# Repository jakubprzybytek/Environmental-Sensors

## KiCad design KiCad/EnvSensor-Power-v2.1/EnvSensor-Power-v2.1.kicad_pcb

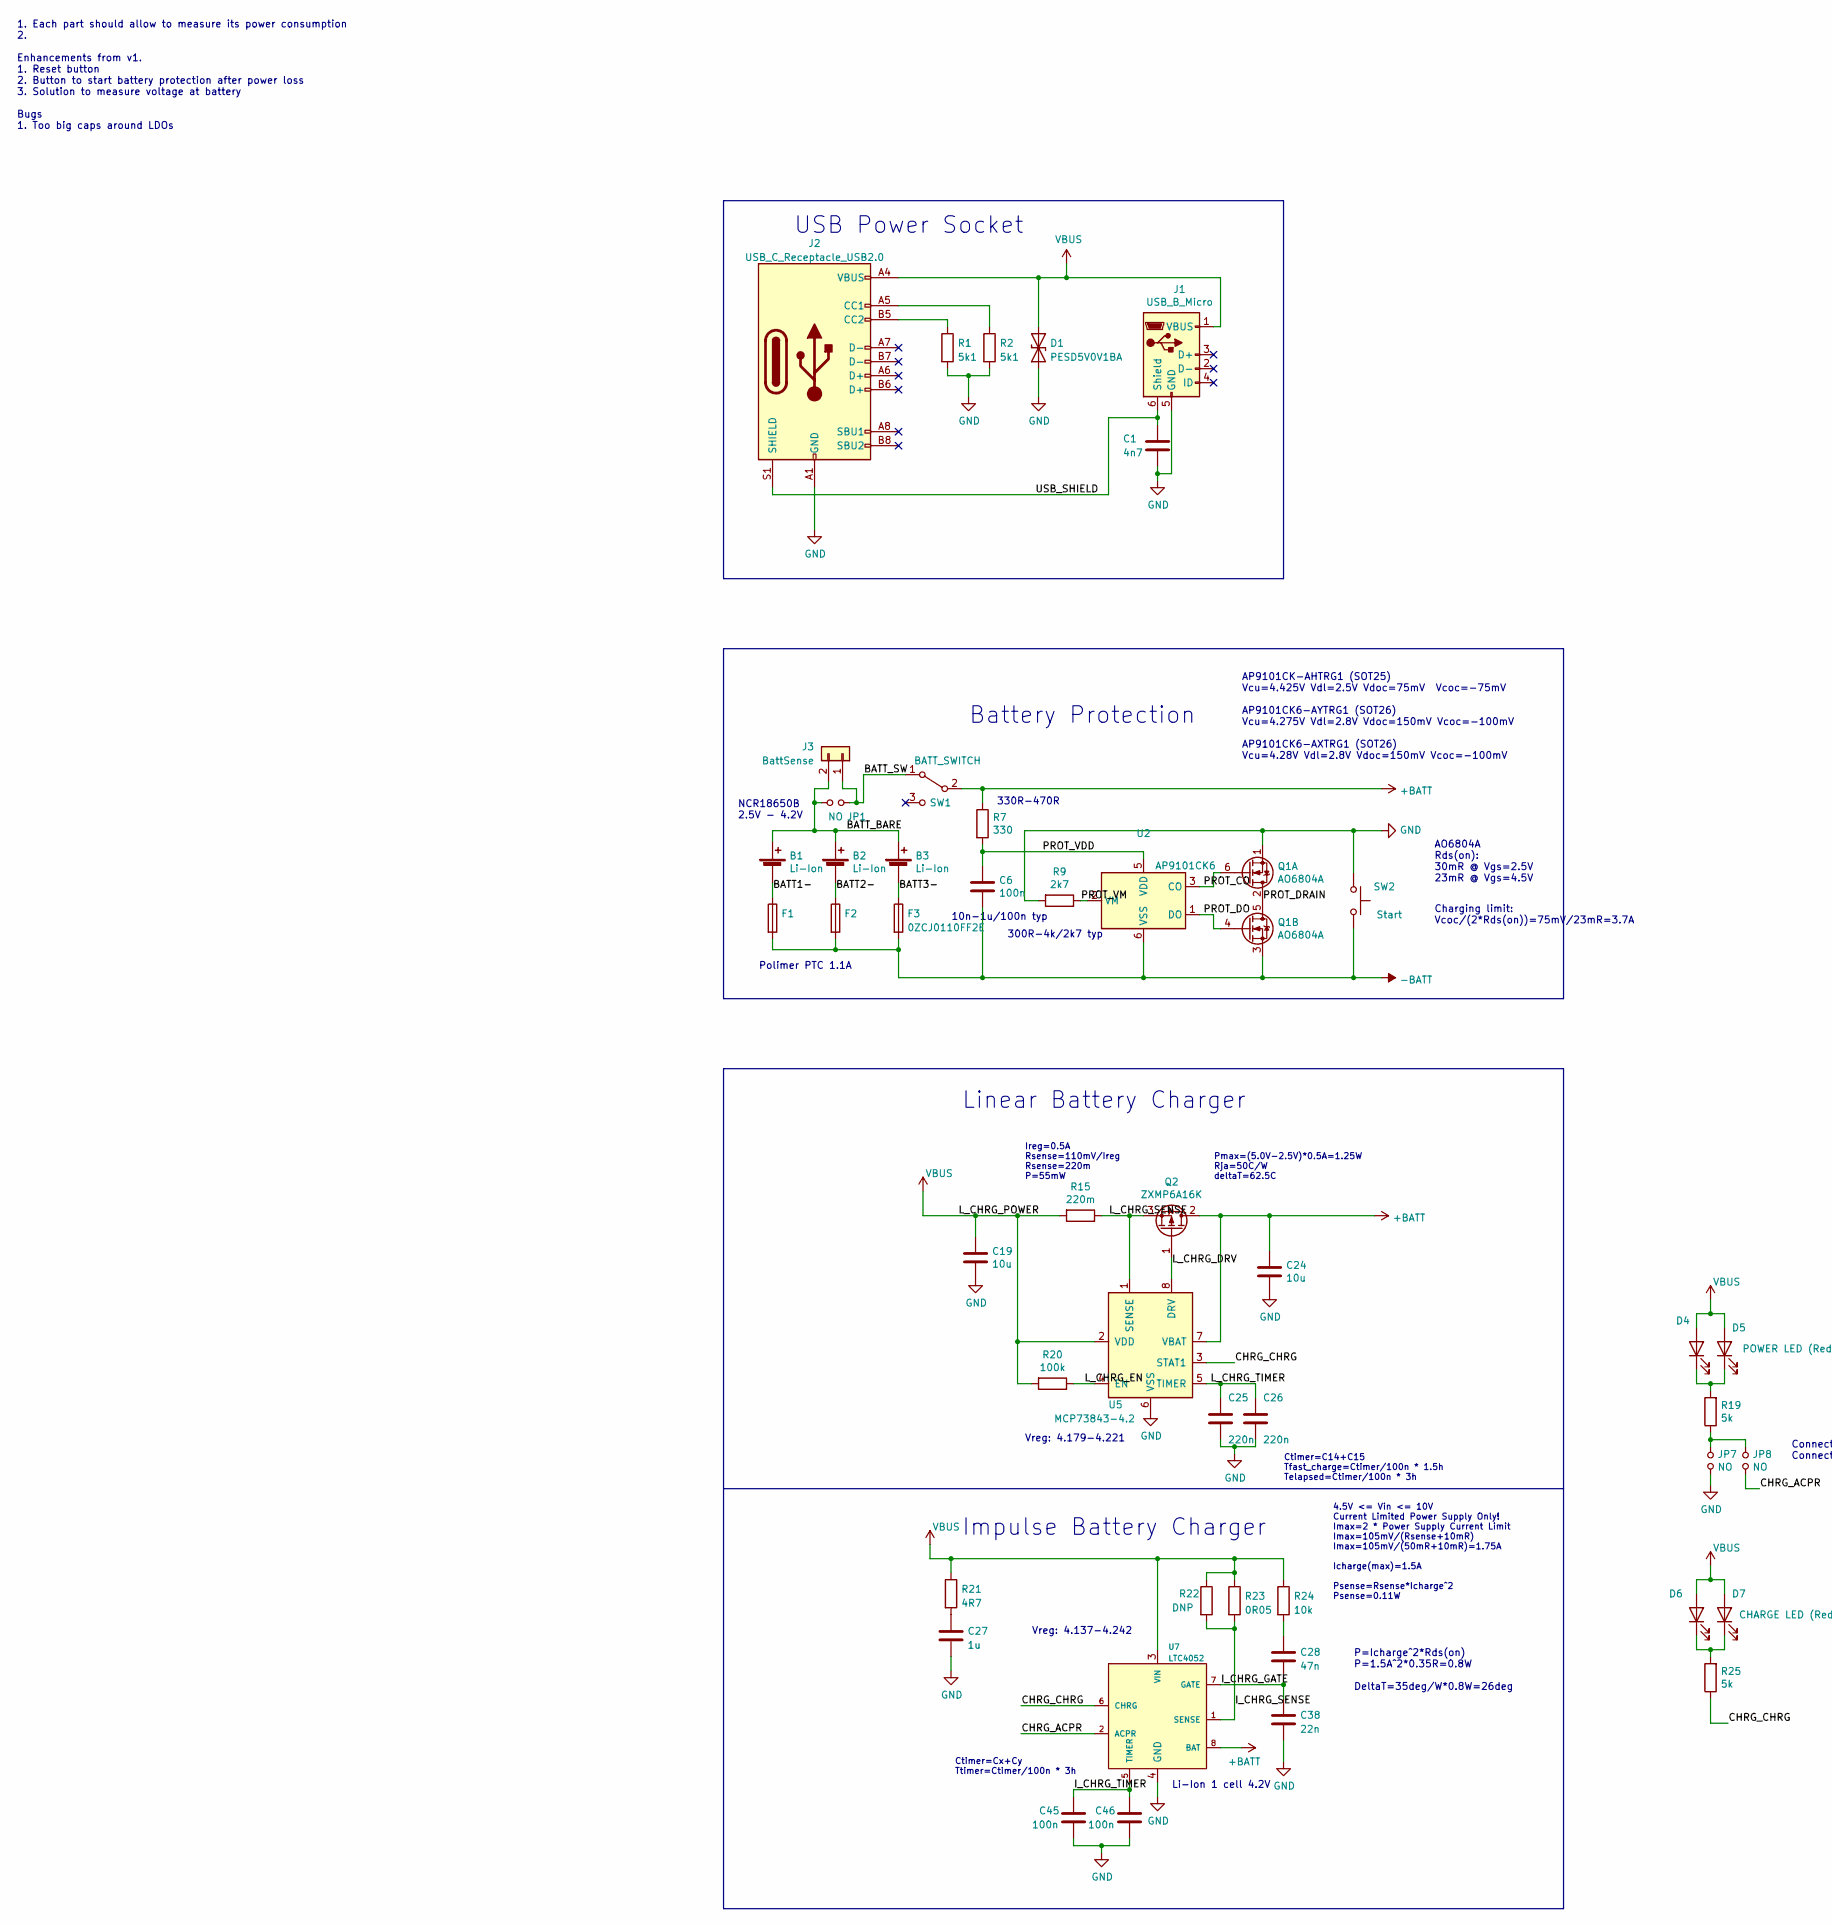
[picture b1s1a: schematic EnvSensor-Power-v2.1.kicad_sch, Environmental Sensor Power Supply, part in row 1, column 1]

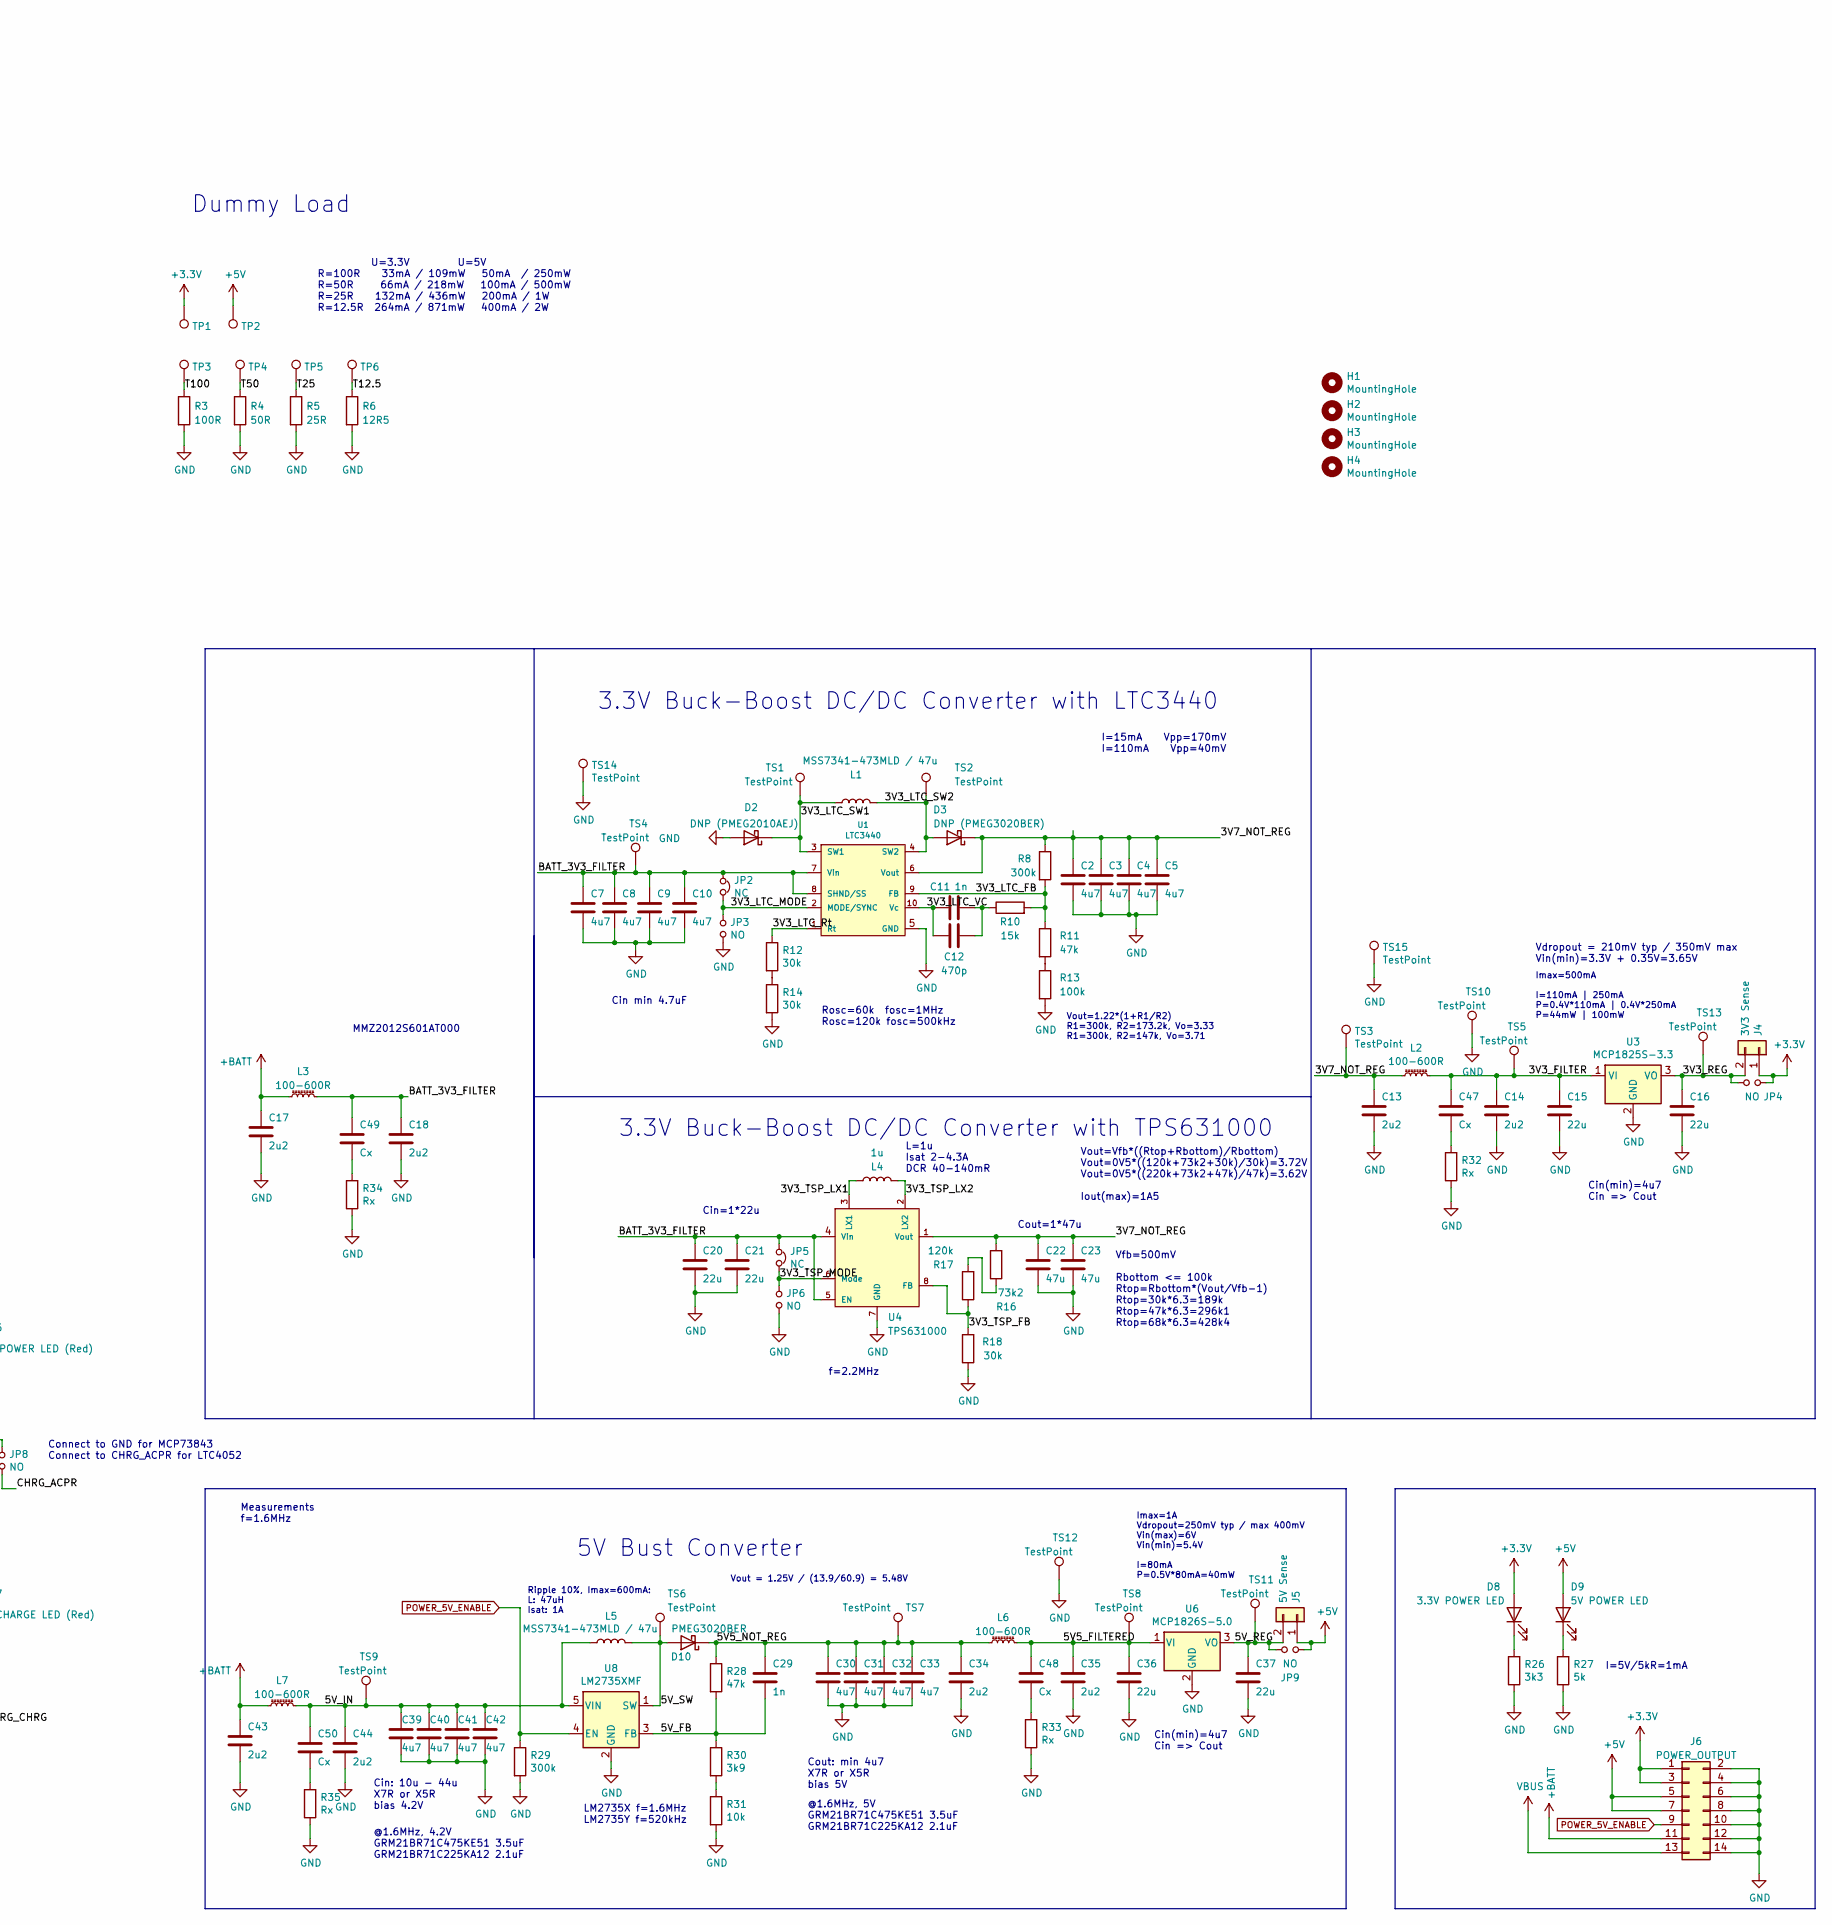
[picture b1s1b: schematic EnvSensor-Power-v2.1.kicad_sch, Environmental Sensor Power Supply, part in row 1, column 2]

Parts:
B1, B2, B3: Li-Ion; BatteryHolder_Keystone_1042_1x18650
C1: 4n7; C_0805_2012Metric
C2, C3, C4, C5, C7, C8, C9, C10, C30, C31, C32, C33, C39, C40, C41, C42: 4u7; C_0805_2012Metric
C6, C45, C46: 100n; C_0603_1608Metric
C11, C29: 1n; C_0805_2012Metric
C12: 470p; C_0805_2012Metric
C13, C14, C17, C18, C34, C35, C43, C44: 2u2; C_0805_2012Metric
C15, C16, C20, C21, C36, C37: 22u; C_1206_3216Metric
C19, C24: 10u; C_0805_2012Metric
C22, C23: 47u; C_1206_3216Metric
C25, C26: 220n; C_0805_2012Metric
C27: 1u; C_0805_2012Metric
C28: 47n; C_0805_2012Metric
C38: 22n; C_0805_2012Metric
C47, C48, C49, C50: Cx; C_0805_2012Metric
D1: PESD5V0V1BA; D_SOD-323_HandSoldering
D2: DNP (PMEG2010AEJ); D_SOD-323_HandSoldering
D3: DNP (PMEG3020BER); D_SOD-123
D4: POWER LED (Red); LED_0805_2012Metric
D5: POWER LED (Red); LED_D3.0mm_Horizontal_O3.81mm_Z6.0mm
D6: CHARGE LED (Red); LED_0805_2012Metric
D7: CHARGE LED (Red); LED_D3.0mm_Horizontal_O3.81mm_Z6.0mm
D8: 3.3V POWER LED; LED_0805_2012Metric
D9: 5V POWER LED; LED_0805_2012Metric
D10: PMEG3020BER; D_SOD-123
F1, F2, F3: 0ZCJ0110FF2E; Fuse_1206_3216Metric
H1, H2, H3, H4: MountingHole; MountingHole_3.2mm_M3
J1: USB_B_Micro; USB_Micro-B_Molex_47346-0001
J2: USB_C_Receptacle_USB2.0; USB_C_Receptacle_GCT_USB4135-GF-A_6P_TopMnt_Horizontal
J3: BattSense; PinHeader_1x02_P2.54mm_Horizontal
J4: 3V3 Sense; PinHeader_1x02_P2.54mm_Horizontal
J5: 5V Sense; PinHeader_1x02_P2.54mm_Horizontal
J6: POWER_OUTPUT; PinHeader_2x07_P2.54mm_Vertical
JP1, JP3, JP4, JP6, JP7, JP8, JP9: NO; SolderJumper-2_P1.3mm_Open_RoundedPad1.0x1.5mm
JP2, JP5: NC; SolderJumper-2_P1.3mm_Bridged_RoundedPad1.0x1.5mm
L1, L5: MSS7341-473MLD / 47u; L_Bourns-SRN8040_8x8.15mm
L2, L3, L6, L7: 100-600R; L_0805_2012Metric
L4: 1u; L_0805_2012Metric
Q1: AO6804A; TSOT-23-6
Q2: ZXMP6A16K; TO-252-2
R1, R2: 5k1; R_0805_2012Metric
R3: 100R; R_2512_6332Metric
R4: 50R; R_2512_6332Metric
R5: 25R; R_2512_6332Metric
R6: 12R5; R_2512_6332Metric
R7: 330; R_0805_2012Metric
R8, R29: 300k; R_0805_2012Metric
R9: 2k7; R_0805_2012Metric
R10: 15k; R_0805_2012Metric
R11, R28: 47k; R_0805_2012Metric
R12, R14, R18: 30k; R_0805_2012Metric
R13: 100k; R_0805_2012Metric
R15: 220m; R_1206_3216Metric
R16: 73k2; R_0805_2012Metric
R17: 120k; R_0805_2012Metric
R19, R25, R27: 5k; R_0805_2012Metric
R20: 100k; R_0603_1608Metric
R21: 4R7; R_0805_2012Metric
R22: DNP; R_1206_3216Metric
R23: 0R05; R_1206_3216Metric
R24: 10k; R_0603_1608Metric
R26: 3k3; R_0805_2012Metric
R30: 3k9; R_0805_2012Metric
R31: 10k; R_0805_2012Metric
R32, R33, R34, R35: Rx; R_0805_2012Metric
SW1: BATT_SWITCH; SW_Lever_1P2T_NKK_GW12LxH
SW2: Start; SW_SPST_CK_RS282G05A3
TP1, TP2, TP3, TP4, TP5, TP6: TestPoint; TestPoint_THTPad_D1.5mm_Drill0.7mm
TS1, TS2, TS3, TS4, TS5, TS6, TS7, TS8, TS9, TS10, TS11, TS12, TS13, TS14, TS15: TestPoint; TestPoint_THTPad_D1.5mm_Drill0.7mm
U1: LTC3440; MSOP-10_3x3mm_P0.5mm
U2: AP9101CK6; SOT-23-6
U3: MCP1825S-3.3; SOT-223-3_TabPin2
U4: TPS631000; SOT-5x3
U5: MCP73843-4.2; MSOP-8_3x3mm_P0.65mm
U6: MCP1826S-5.0; SOT-223-3_TabPin2
U7: LTC4052; MSOP-8_3x3mm_P0.65mm
U8: LM2735XMF; SOT-23-5

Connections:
+3V3: D8.2 (A), J4.1, J6.1, J6.3, JP4.2, TP1.1
+5V: D9.2 (A), J5.1, J6.5, J6.7, JP9.2, TP2.1
+BATT: C17.1, C24.1, C43.1, J6.11, L3.1, L7.1, Q2.2 (D), R7.1, SW1.2 (B), U5.7 (VBAT), U7.8 (BAT)
-BATT: C6.2, F1.2, F2.2, F3.2, Q1.3 (S2), SW2.1, U2.6 (VSS)
/3V3_FILTER: C14.1, C15.1, C47.1, L2.2, TS5.1, U3.1 (VI)
/3V3_LTC_FB: R8.2, R10.2, R11.1, U1.9 (FB)
/3V3_LTC_MODE: JP2.2, JP3.1, U1.2 (MODE/SYNC)
/3V3_LTC_Rt: R12.1, U1.1 (Rt)
/3V3_LTC_SW1: D2.1 (K), L1.1, TS1.1, U1.3 (SW1)
/3V3_LTC_SW2: D3.2 (A), L1.2, TS2.1, U1.4 (SW2)
/3V3_LTC_VC: C11.2, C12.2, U1.10 (Vc)
/3V3_REG: C16.1, J4.2, JP4.1, TS13.1, U3.3 (VO)
/3V3_TSP_FB: R17.1, R18.2, U4.8 (FB)
/3V3_TSP_LX1: L4.1, U4.3 (LX1)
/3V3_TSP_LX2: L4.2, U4.2 (LX2)
/3V3_TSP_MODE: JP5.2, JP6.1, U4.6 (Mode)
/3V7_NOT_REG: C2.1, C3.1, C4.1, C5.1, C13.1, C22.1, C23.1, D3.1 (K), L2.1, R8.1, R16.2, TS3.1, U1.6 (Vout), U4.1 (Vout)
/5V5_FILTERED: C35.1, C36.1, C48.1, L6.2, TS8.1, U6.1 (VI)
/5V5_NOT_REG: C29.1, C30.1, C31.1, C32.1, C33.1, C34.1, D10.1 (K), L6.1, R28.1, TS7.1
/5V_FB: C29.2, R28.2, R30.1, U8.3 (FB)
/5V_IN: C39.1, C40.1, C41.1, C42.1, C44.1, C50.1, L5.1, L7.2, TS9.1, U8.5 (VIN); also elsewhere on the board
/5V_REG: C37.1, J5.2, JP9.1, TS11.1, U6.3 (VO)
/5V_SW: D10.2 (A), L5.2, TS6.1, U8.1 (SW)
/BATT1-: B1.2 (-), F1.1
/BATT2-: B2.2 (-), F2.1
/BATT3-: B3.2 (-), F3.1
/BATT_3V3_FILTER: C7.1, C8.1, C9.1, C10.1, C18.1, C20.1, C21.1, C49.1, JP2.1, JP5.1, L3.2, TS4.1, U1.7 (Vin), U1.8 (SHND/SS), U4.4 (Vin), U4.5 (EN)
/BATT_BARE: B1.1 (+), B2.1 (+), B3.1 (+), J3.2, JP1.1
/BATT_SW: J3.1, JP1.2, SW1.1 (A)
/CHRG_ACPR: JP8.2, U7.2 (ACPR)
/CHRG_CHRG: R25.1, U5.3 (STAT1), U7.6 (CHRG)
/I_CHRG_GATE: C28.2, C38.1, U7.7 (GATE)
/I_CHRG_SENSE: R22.2, R23.2, U7.1 (SENSE)
/I_CHRG_TIMER: C45.1, C46.1, U7.5 (TIMER)
/L_CHRG_DRV: Q2.1 (G), U5.8 (DRV)
/L_CHRG_EN: R20.1, U5.4 (EN)
/L_CHRG_SENSE: Q2.3 (S), R15.1, U5.1 (SENSE)
/L_CHRG_TIMER: C25.1, C26.1, U5.5 (TIMER)
/PROT_CO: Q1.6 (G2), U2.3 (CO)
/PROT_DO: Q1.4 (G2), U2.1 (DO)
/PROT_DRAIN: Q1.2 (D2), Q1.5 (D2)
/PROT_VDD: C6.1, R7.2, U2.5 (VDD)
/PROT_VM: R9.1, U2.2 (VM)
/T12.5: R6.1, TP6.1
/T25: R5.1, TP5.1
/T50: R4.1, TP4.1
/T100: R3.1, TP3.1
/USB_SHIELD: C1.1, J1.6 (Shield), J2.S1 (SHIELD)
GND: C1.2, C2.2, C3.2, C4.2, C5.2, C7.2, C8.2, C9.2, C10.2, C13.2, C14.2, C15.2, C16.2, C17.2, C18.2, C19.2, C20.2, C21.2, C22.2, C23.2, C24.2, C25.2, C26.2, C27.2, C30.2, C31.2, C32.2, C33.2, C34.2, C35.2, C36.2, C37.2, C38.2, C39.2, C40.2, C41.2, C42.2, C43.2, C44.2, C45.2, C46.2, D1.1 (A1), D2.2 (A), J1.5 (GND), J2.A1 (GND), J2.A12 (GND), J2.B1 (GND), J2.B12 (GND), J6.2, J6.4, J6.6, J6.8, J6.10, J6.12, J6.14, JP3.2, JP6.2, JP7.2, Q1.1 (S2), R1.2, R2.2, R3.2, R4.2, R5.2, R6.2, R9.2, R13.2, R14.2, R18.1, R26.1, R27.1, R29.2, R31.2, R32.1, R33.1, R34.1, R35.1, SW2.2, TS10.1, TS12.1, TS14.1, TS15.1, U1.5 (GND), U3.2 (GND), U4.7 (GND), U5.6 (VSS), U6.2 (GND), U7.4 (GND), U8.2 (GND)
unnamed: C11.1, C12.1, R10.1
unnamed: C27.1, R21.2
unnamed: C28.1, R24.2
unnamed: C47.2, R32.2
unnamed: C48.2, R33.2
unnamed: C49.2, R34.2
unnamed: C50.2, R35.2
unnamed: D4.1 (K), D5.1 (K), R19.2
unnamed: D6.1 (K), D7.1 (K), R25.2
unnamed: D8.1 (K), R26.2
unnamed: D9.1 (K), R27.2
unnamed: J2.A5 (CC1), R2.1
unnamed: J2.B5 (CC2), R1.1
unnamed: JP7.1, JP8.1, R19.1
unnamed: R11.2, R13.1
unnamed: R12.2, R14.1
unnamed: R16.1, R17.2
unnamed: R30.2, R31.1
POWER_5V_ENABLE: J6.9, R29.1, U8.4 (EN)
VBUS: C19.1, D1.2 (A2), D4.2 (A), D5.2 (A), D6.2 (A), D7.2 (A), J1.1 (VBUS), J2.A4 (VBUS), J2.A9 (VBUS), J2.B4 (VBUS), J2.B9 (VBUS), J6.13, R15.2, R20.2, R21.1, R22.1, R23.1, R24.1, U5.2 (VDD), U7.3 (VIN)

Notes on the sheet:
Ripple 10%, Imax=600mA: L: 47uH Isat: 1A
AP9101CK-AHTRG1 (SOT25) Vcu=4.425V Vdl=2.5V Vdoc=75mV Vcoc=-75mV AP9101CK6-AYTRG1 (SOT26) Vcu=4.275V Vdl=2.8V Vdoc=150mV Vcoc=-100mV AP9101CK6-AXTRG1 (SOT26) Vcu=4.28V Vdl=2.8V Vdoc=150mV Vcoc=-100mV
Cout: min 4u7 X7R or X5R bias 5V
1. Each part should allow to measure its power consumption 2. Enhancements from v1. 1. Reset button 2. Button to start battery protection after power loss 3. Solution to measure voltage at battery Bugs 1. Too big caps around LDOs
Linear Battery Charger
Connect to GND for MCP73843 Connect to CHRG_ACPR for LTC4052
330R-470R
5V Bust Converter
Ireg=0.5A Rsense=110mV/Ireg Rsense=220m P=55mW
MMZ2012S601AT000
Pmax=(5.0V-2.5V)*0.5A=1.25W Rja=50C/W deltaT=62.5C
Ctimer=Cx+Cy Ttimer=Ctimer/100n * 3h
Vfb=500mV Rbottom <= 100k Rtop=Rbottom*(Vout/Vfb-1) Rtop=30k*6.3=189k Rtop=47k*6.3=296k1 Rtop=68k*6.3=428k4
I=15mA Vpp=170mV I=110mA Vpp=40mV
Li-Ion 1 cell 4.2V
3.3V Buck-Boost DC/DC Converter with LTC3440
Impulse Battery Charger
Cin(min)=4u7 Cin => Cout
Cin min 4.7uF
Imax=500mA I=110mA | 250mA P=0.4V*110mA | 0.4V*250mA P=44mW | 100mW
I=5V/5kR=1mA
Cout=1*47u
@1.6MHz, 4.2V GRM21BR71C475KE51 3.5uF GRM21BR71C225KA12 2.1uF
AO6804A Rds(on): 30mR @ Vgs=2.5V 23mR @ Vgs=4.5V
USB Power Socket
4.5V <= Vin <= 10V Current Limited Power Supply Only! Imax=2 * Power Supply Current Limit Imax=105mV/(Rsense+10mR) Imax=105mV/(50mR+10mR)=1.75A Icharge(max)=1.5A Psense=Rsense*Icharge^2 Psense=0.11W
Rosc=60k fosc=1MHz Rosc=120k fosc=500kHz
Cin=1*22u
Ctimer=C14+C15 Tfast_charge=Ctimer/100n * 1.5h Telapsed=Ctimer/100n * 3h
Dummy Load
L=1u Isat 2-4.3A DCR 40-140mR
3.3V Buck-Boost DC/DC Converter with TPS631000
f=2.2MHz
Vreg: 4.179-4.221
Vdropout = 210mV typ / 350mV max Vin(min)=3.3V + 0.35V=3.65V
Cin: 10u - 44u X7R or X5R bias 4.2V
Vout=1.22*(1+R1/R2) R1=300k, R2=173.2k, Vo=3.33 R1=300k, R2=147k, Vo=3.71
P=Icharge^2*Rds(on) P=1.5A^2*0.35R=0.8W DeltaT=35deg/W*0.8W=26deg
U=3.3V U=5V R=100R 33mA / 109mW 50mA / 250mW R=50R 66mA / 218mW 100mA / 500mW R=25R 132mA / 436mW 200mA / 1W R=12.5R 264mA / 871mW 400mA / 2W
Imax=1A Vdropout=250mV typ / max 400mV Vin(max)=6V Vin(min)=5.4V I=80mA P=0.5V*80mA=40mW

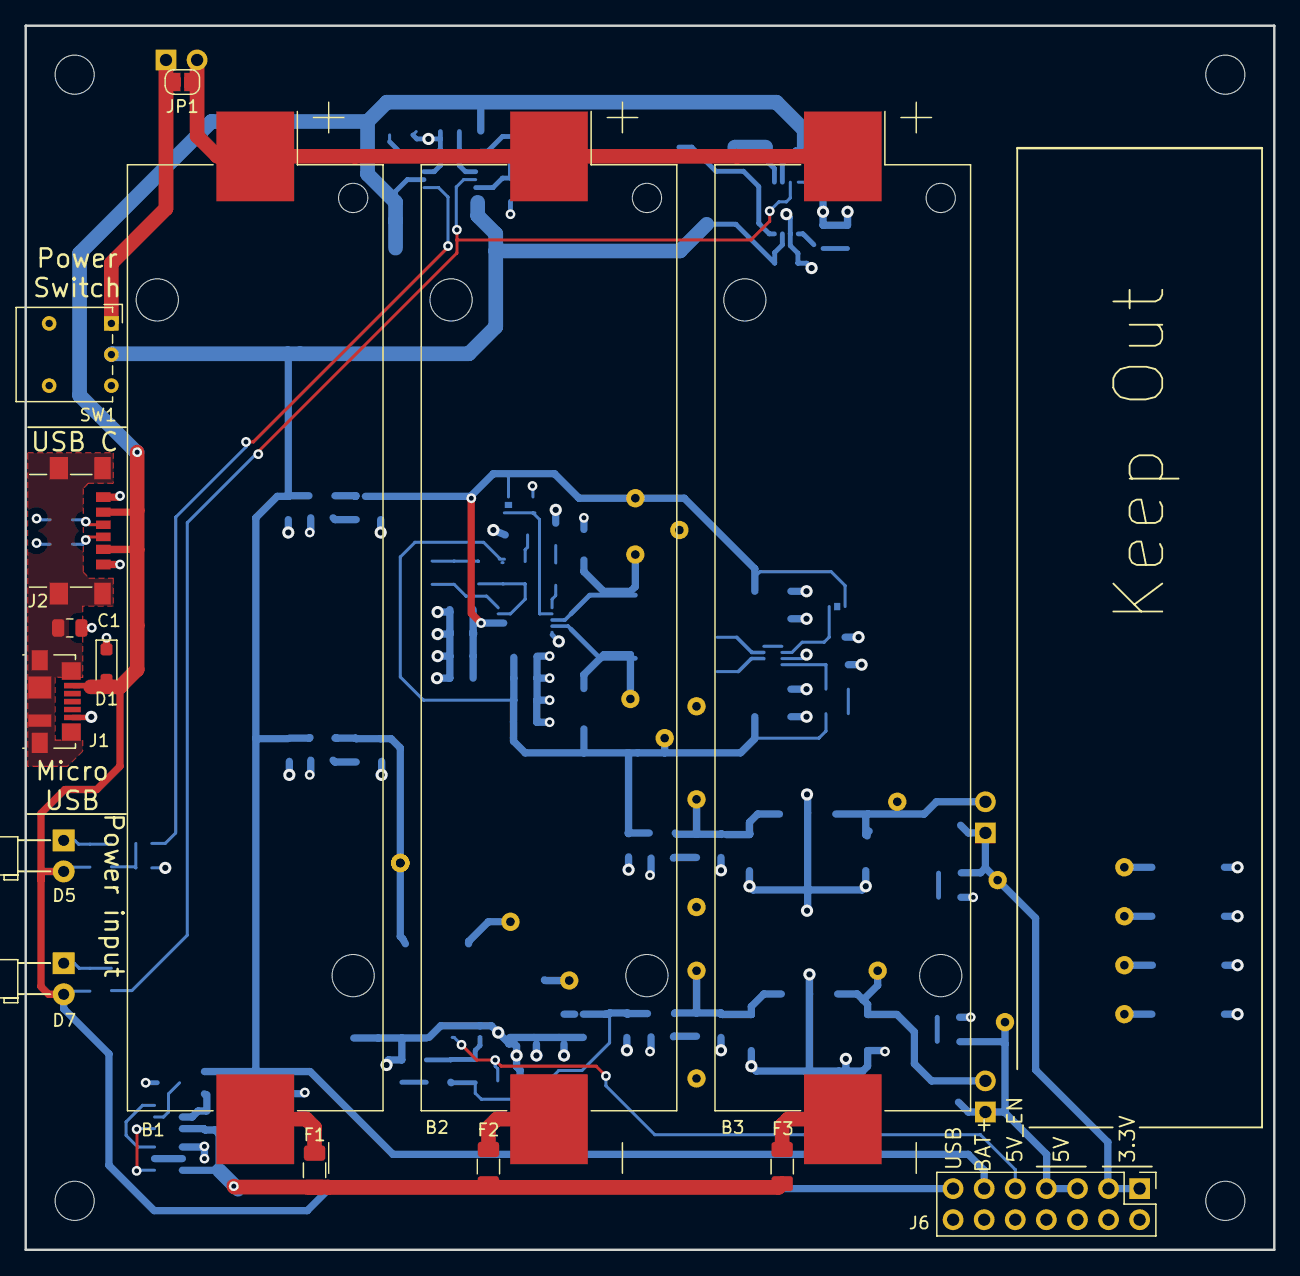
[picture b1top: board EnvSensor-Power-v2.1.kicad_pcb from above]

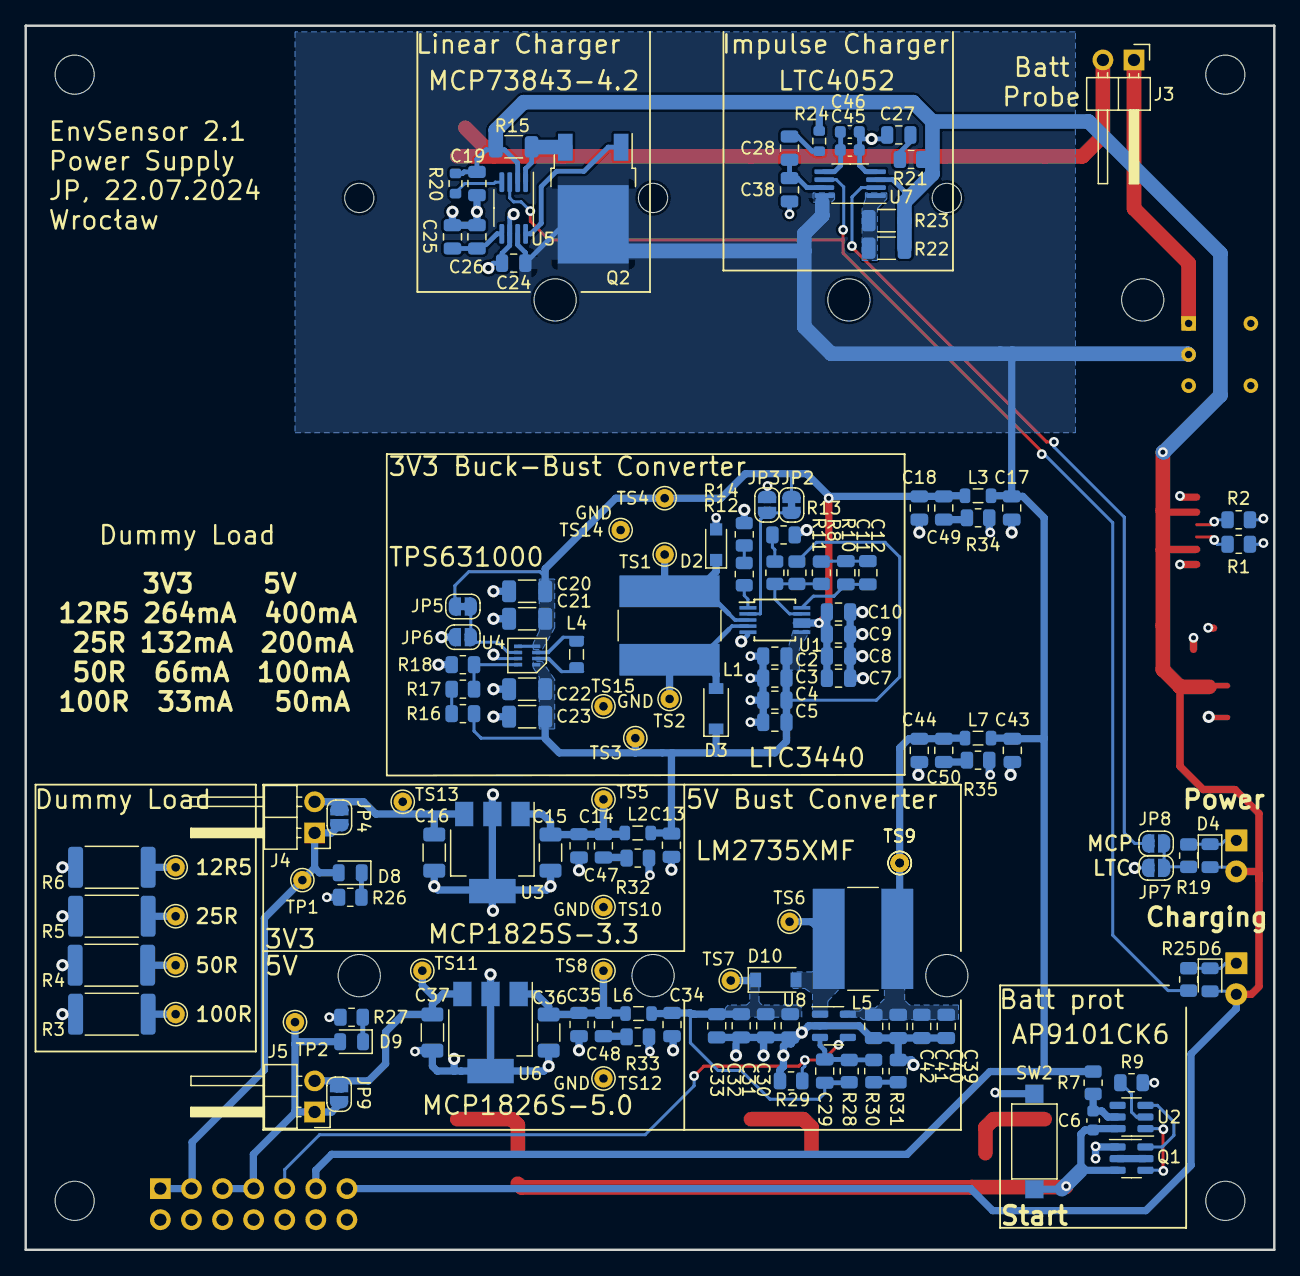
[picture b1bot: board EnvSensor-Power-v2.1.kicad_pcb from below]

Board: 4 copper layers, 102.0 x 100.0 mm, 161 parts (142 on the bottom side), 69 nets.

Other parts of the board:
TS9#2: TestPoint; TestPoint_THTPad_D1.5mm_Drill0.7mm

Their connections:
/5V_IN: TS9#2.1; also elsewhere on the board

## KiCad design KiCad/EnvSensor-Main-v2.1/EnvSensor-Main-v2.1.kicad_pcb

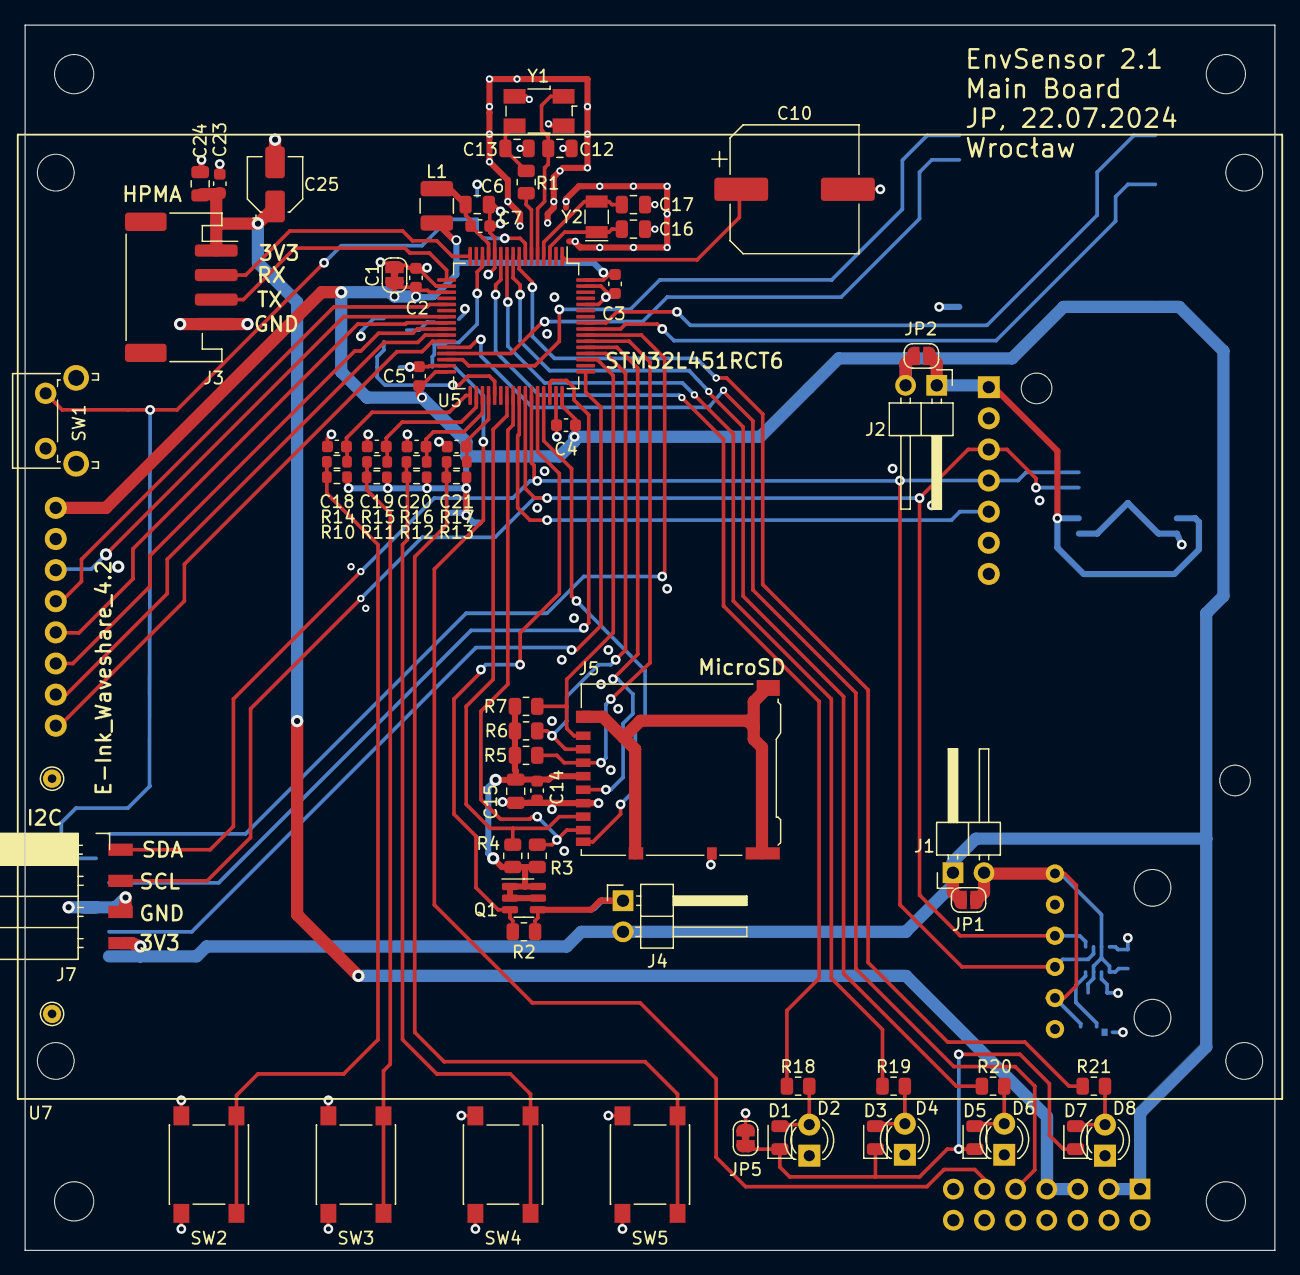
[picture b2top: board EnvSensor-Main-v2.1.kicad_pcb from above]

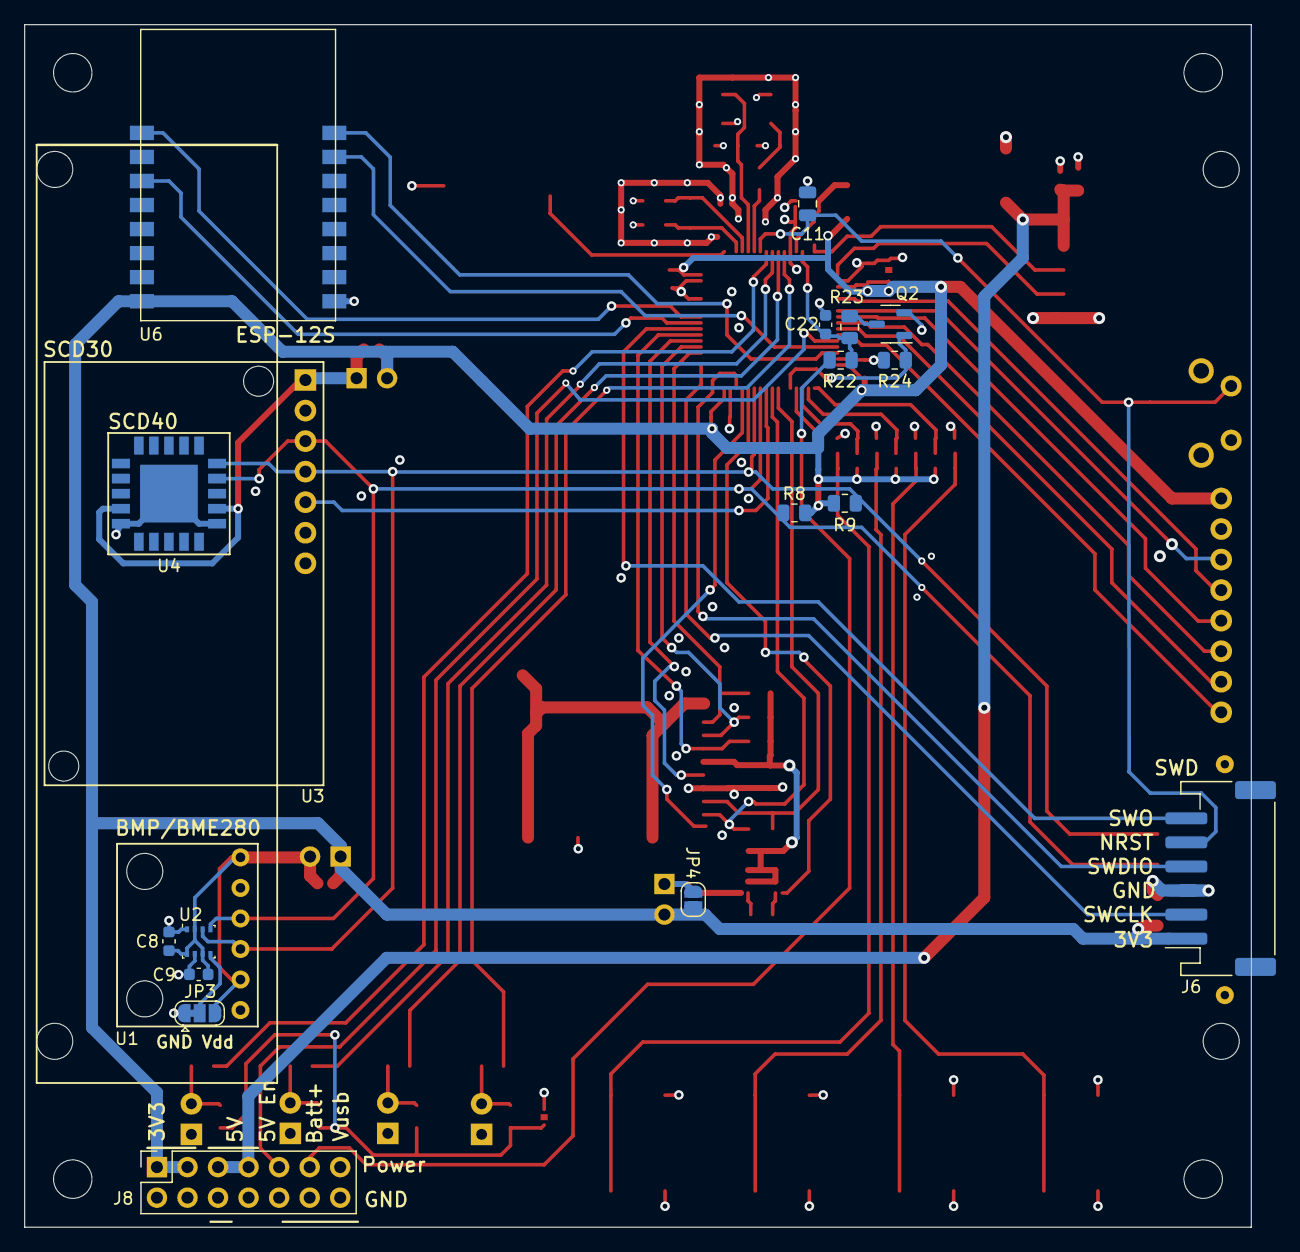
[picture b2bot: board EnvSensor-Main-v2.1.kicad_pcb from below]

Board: 4 copper layers, 102.0 x 100.0 mm, 93 parts (19 on the bottom side), 64 nets.

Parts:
C1: 10u; SolderJumper-2_P1.3mm_Bridged_RoundedPad1.0x1.5mm
C2, C3, C4, C5, C7, C8, C9, C14, C18, C19, C20, C21, C22, C23: 100n; C_0603_1608Metric
C6: 1u; C_0805_2012Metric
C10: SuperCap; CP_Elec_10x7.7
C11, C24: 10n; C_0805_2012Metric
C12, C13: 6p; C_0805_2012Metric
C15: 10u; C_0805_2012Metric
C16, C17: 15p; C_0805_2012Metric
C25: 22u; CP_Elec_4x5.3
D1: CPU_LED; LED_0805_2012Metric
D2, D4, D6, D8: LED; LED_D3.0mm
D3: SD_LED; LED_0805_2012Metric
D5, D7: LED; LED_0805_2012Metric
H1, H2, H3, H4: MountingHole; MountingHole_3.2mm_M3
H5, H6: MountingHole; TestPoint_THTPad_D1.5mm_Drill0.7mm
J1, J2, J4: Conn_01x02; PinHeader_1x02_P2.54mm_Horizontal
J3: HPMA115C0-003; JST_PH_S4B-PH-SM4-TB_1x04-1MP_P2.00mm_Horizontal
J5: Micro_SD_Card_Det; microSD_HC_Hirose_DM3AT-SF-PEJM5
J6: SWD; JST_PH_S6B-PH-SM4-TB_1x06-1MP_P2.00mm_Horizontal
J7: I2C; PinSocket_1x04_P2.54mm_Horizontal_SMD
J8: POWER_INPUT; PinSocket_2x07_P2.54mm_Vertical
JP1, JP2, JP4: NO; SolderJumper-2_P1.3mm_Open_RoundedPad1.0x1.5mm
JP3: Address; SolderJumper-3_P1.3mm_Bridged12_RoundedPad1.0x1.5mm
JP5: NC; SolderJumper-2_P1.3mm_Bridged_RoundedPad1.0x1.5mm
L1: 10u; L_1210_3225Metric
Q1: Si3407DV; TSOT-23-6
Q2: IRLML2502; SOT-23-3
R1, R18, R19, R20, R21: 2k2; R_0805_2012Metric
R2: 300k; R_0805_2012Metric
R3, R4, R5, R6, R7: 33k; R_0805_2012Metric
R8, R9, R23: 10k; R_0805_2012Metric
R10, R11, R12, R13, R14, R15, R16, R17: 10k; R_0603_1608Metric
R22: 3k; R_0805_2012Metric
R24: 100k; R_0805_2012Metric
SW1: Reset; SW_Tactile_SPST_Angled_PTS645Vx83-2LFS
SW2, SW3, SW4, SW5: SW_Push; SW_SPST_PTS645
U1: BME280-Module
U2: BMP280; Bosch_LGA-8_2.5x2.5mm_P0.65mm_ClockwisePinNumbering
U3: SCD30
U4: SCD40; SCD4x
U5: STM32L451RCT6; LQFP-64_10x10mm_P0.5mm
U6: ESP-12S
U7: E-Ink_Waveshare_4.2; 4.2inch_E-Ink
Y1: 16MHz; Crystal_SMD_Abracon_ABM3B-4Pin_5.0x3.2mm
Y2: 32768/12.5pF; Crystal_SMD_MicroCrystal_CC7V-T1A-2Pin_3.2x1.5mm

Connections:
+3.3VA: C6.1, C7.1, L1.2, U5.13 (VDDA)
+3V3: C1.1, C2.1, C3.1, C4.1, C5.1, J1.1, J2.2, J4.2, J6.1, J7.4, J8.1, J8.3, JP1.2, JP2.2, JP4.1, L1.1, R8.2, R9.2, R10.1, R11.1, R12.1, R13.1, U5.19 (VDD), U5.32 (VDD), U5.48 (VDDUSB), U5.64 (VDD), U6.8 (VCC), U7.1 (VDD)
+5V: C23.1, C24.1, C25.1, J3.1, J8.5, J8.7
+BATT: J8.11, R22.1
/BMP280_VCC: C8.1, C9.1, J1.2, JP1.1, JP3.3 (B), U1.1 (VDD), U1.5 (CSB), U2.2 (CSB), U2.6 (VDDIO), U2.8 (VDD)
/SCD_POWER: J2.1, JP2.1, U3.1 (VDD), U4.7 (VDD), U4.19 (VDDH)
/SD_3V3: C14.2, C15.2, J5.4 (VDD), Q1.1 (D), Q1.2 (D), Q1.5 (D), Q1.6 (D), R3.2, R4.2, R5.2, R6.2, R7.2
/VBAT: C10.1, U5.1 (VBAT)
BATTERY_MEASURE_ENABLE: Q2.1 (G), R24.1, U5.37 (PC6)
BATTERY_MEASURE_INPUT: C22.1, R22.2, R23.1, U5.14 (PA0)
E_INK_BUSY: U5.27 (PB1), U7.8 (BUSY)
E_INK_DC: U5.25 (PC5), U7.6 (DC)
E_INK_RESET: U5.26 (PB0), U7.7 (RST)
E_INK_SELECT: U5.24 (PC4), U7.5 (CS)
GND: C1.2, C2.2, C3.2, C4.2, C5.2, C6.2, C7.2, C8.2, C9.2, C10.2, C11.1, C12.2, C13.2, C14.1, C15.1, C16.2, C17.2, C18.2, C19.2, C20.2, C21.2, C22.2, C23.2, C24.2, C25.2, D2.1 (K), D4.1 (K), D6.1 (K), D8.1 (K), J3.4, J5.6 (VSS), J5.10 (DET_A), J6.3, J7.3, J8.2, J8.4, J8.6, J8.8, J8.10, J8.12, J8.14, JP3.1 (A), JP5.2 (B), Q2.2 (S), R24.2, SW1.1, SW2.1, SW3.1, SW4.1, SW5.1, U1.2 (GND), U1.6 (SDO), U2.1 (GND), U2.7 (GND), U3.2 (GND), U3.7 (SEL), U4.6 (GND), U4.20 (GND), U4.21 (GND), U5.12 (VSSA), U5.18 (VSS), U5.31 (VSS), U5.47 (VSS), U5.60 (PH3), U5.63 (VSS), U6.9 (GND), U7.2 (GND), Y1.2, Y1.4
HPMA_RX: J3.2, U5.16 (PA2)
HPMA_TX: J3.3, U5.17 (PA3)
LED_1: R18.1, U5.11 (PC3)
LED_2: R19.1, U5.10 (PC2)
LED_3: R20.1, U5.9 (PC1)
LED_4: R21.1, U5.8 (PC0)
MOSI: U5.23 (PA7), U7.3 (DIN)
NRST: C11.2, J6.5, SW1.2, U5.7 (NRST)
unnamed: C13.1, R1.2, Y1.3
unnamed: D1.2 (A), D2.2 (A), R18.2
unnamed: D1.1 (K), D3.1 (K), D5.1 (K), D7.1 (K), JP5.1 (A)
unnamed: D3.2 (A), D4.2 (A), R19.2
unnamed: D5.2 (A), D6.2 (A), R20.2
unnamed: D7.2 (A), D8.2 (A), R21.2
unnamed: J4.1, JP4.2, Q1.4 (S), R2.1
unnamed: JP3.2 (C), U2.5 (SDO)
unnamed: Q2.3 (D), R23.2
unnamed: R10.2, R14.2, SW2.2
unnamed: R11.2, R15.2, SW3.2
unnamed: R12.2, R16.2, SW4.2
unnamed: R13.2, R17.2, SW5.2
unnamed: C16.1, U5.3 (PC14), Y2.1
unnamed: C17.1, U5.4 (PC15), Y2.2
unnamed: C12.1, U5.5 (PH0), Y1.1
unnamed: R1.1, U5.6 (PH1)
POWER_5V_ENABLE: J8.9, U5.28 (PB2)
SCD30_READY: U3.5 (RDY), U5.41 (PA8)
SCK: U5.21 (PA5), U7.4 (CLK)
SCL: J7.2, R8.1, U1.3 (SCL), U2.4 (SCK), U3.3 (TX/SCL), U4.9 (SCL), U5.42 (PA9)
SDA: J7.1, R9.1, U1.4 (SDA), U2.3 (SDI), U3.4 (RX/SDA), U4.10 (SDA), U5.43 (PA10)
SDIO_CLK: J5.5 (CLK), U5.53 (PC12)
SDIO_CMD: J5.3 (CMD), R5.1, U5.54 (PD2)
SDIO_DATA0: J5.7 (DAT0), R4.1, U5.39 (PC8)
SDIO_DATA1: J5.8 (DAT1), R3.1, U5.40 (PC9)
SDIO_DATA2: J5.1 (DAT2), R7.1, U5.51 (PC10)
SDIO_DATA3: J5.2 (DAT3/CD), R6.1, U5.52 (PC11)
SDIO_DETECT: J5.9 (DET_B), U5.45 (PA12)
SDIO_POWER_ENABLE: Q1.3 (G), R2.2, U5.44 (PA11)
SWCLK: J6.2, U5.49 (PA14)
SWDIO: J6.4, U5.46 (PA13)
SWITCH_1: C18.1, R14.1, U5.33 (PB12)
SWITCH_2: C19.1, R15.1, U5.34 (PB13)
SWITCH_3: C20.1, R16.1, U5.35 (PB14)
SWITCH_4: C21.1, R17.1, U5.36 (PB15)
SWO: J6.6, U5.55 (PB3)
WFI_TX: U5.30 (PB11), U6.16 (TXD0)
WIFI_ENABLE: U5.56 (PB4), U6.3 (EN)
WIFI_RESET: U5.57 (PB5), U6.1 (Reset)
WIFI_RX: U5.29 (PB10), U6.15 (RXD0)
